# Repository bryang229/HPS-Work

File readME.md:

# About

This is a Clock PCB designed using KiCAD!

The code working with the clock is also included written in the arduino editor!

All parts in the clock are from [this library](https://github.com/hps-matthew/hps-kicad-library) (very useful !).

This is a project under the Hardware Product Spring program ! (Hence HPS) 

More documentation about the code is to come.

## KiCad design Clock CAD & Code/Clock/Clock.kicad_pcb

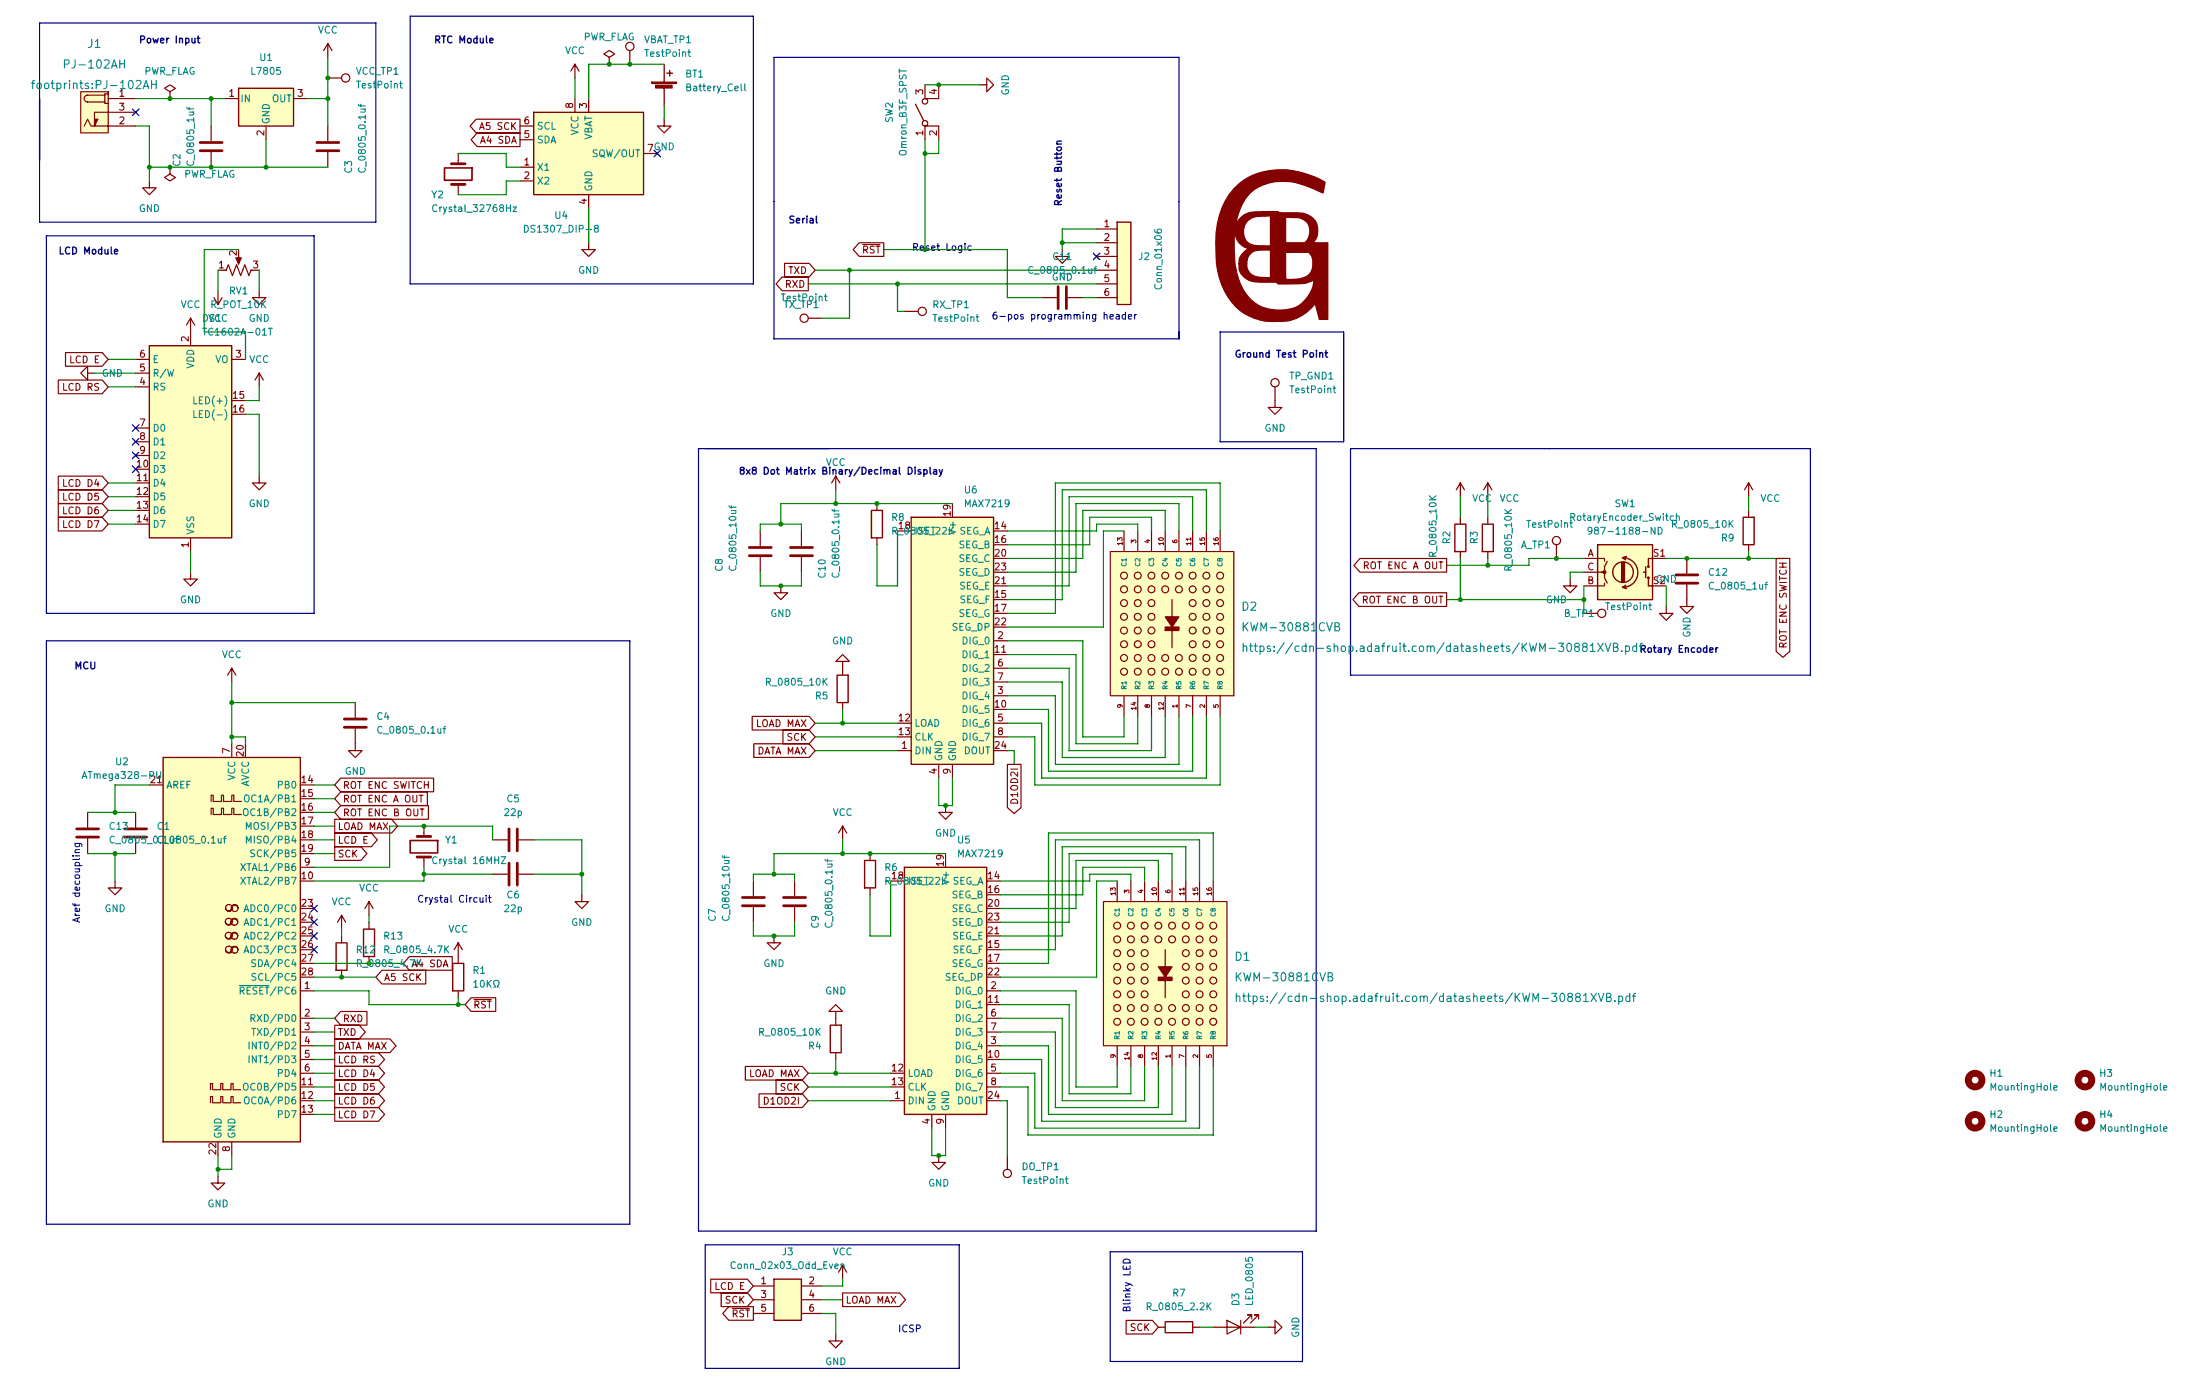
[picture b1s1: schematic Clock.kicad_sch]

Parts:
A_TP1: TestPoint; TestPoint_THTPad_D2.0mm_Drill1.0mm
BT1: Battery_Cell; BatteryHolder_Keystone_106_1x20mm; MPN BS-7; Digikey PN BS-7-ND
B_TP1: TestPoint; TestPoint_THTPad_D2.0mm_Drill1.0mm
C1, C3, C4, C9, C10, C11, C13: C_0805_0.1uf; C_0805_2012Metric; Voltage N/A; Tolerance N/A; MPN 08055C104KAT2A; Digikey PN 478-1395-1-ND
C2, C12: C_0805_1uf; C_0805_2012Metric; Voltage N/A; Tolerance N/A; MPN CC0805KKX7R8BB105; Digikey PN 311-1456-1-ND
C5, C6: 22p; C_0805_2012Metric; Voltage N/A; Tolerance N/A; MPN CC0805JRNPO9BN220; Digikey PN 311-1103-1-ND
C7, C8: C_0805_10uf; C_0805_2012Metric; Voltage N/A; Tolerance N/A; MPN GRM21BR61E106KA73L; Digikey PN 490-5523-1-ND
D1, D2: KWM-30881CVB; MPN KWM-30881CVB; Digikey PN N/A
D3: LED_0805; LED_0805_2012Metric; MPN 150080RS75000; Digikey PN 732-4984-1-ND
DO_TP1: TestPoint; TestPoint_THTPad_D2.0mm_Drill1.0mm
DS1: TC1602A-01T; MPN 1447; Digikey PN 1528-2212-ND
H1, H2, H3, H4: MountingHole; MountingHole_3.2mm_M3
J1: PJ-102AH; MPN PJ-102AH; Digikey PN CP-102AH-ND
J2: Conn_01x06; PinHeader_1x06_P2.54mm_Vertical; MPN 61300611121; Digikey PN 732-5319-ND
J3: Conn_02x03_Odd_Even; PinHeader_2x03_P2.54mm_Vertical; MPN PRPC003DAAN-RC; Digikey PN S2011EC-03-ND
R1: 10KΩ; R_0805_2012Metric; Tolerance N/A; MPN RC0805FR-0710KL; Digikey PN 311-10.0KCRCT-ND
R2, R3, R4, R5, R9: R_0805_10K; R_0805_2012Metric; Tolerance N/A; MPN RC0805FR-0710KL; Digikey PN 311-10.0KCRCT-ND
R6, R8: R_0805_22K; R_0805_2012Metric; Tolerance N/A; MPN RC0805FR-0722KL; Digikey PN 311-22.0KCRCT-ND
R7: R_0805_2.2K; R_0805_2012Metric; Tolerance N/A; MPN N/A; Digikey PN 311-2.20KCRCT-ND
R12, R13: R_0805_4.7K; R_0805_2012Metric; Tolerance N/A; MPN RC0805FR-074K7L; Digikey PN 311-4.70KCRCT-ND
RV1: R_POT_10K; Potentiometer_Bourns_3386P_Vertical; MPN 3386P-1-103TLF; Digikey PN 3386P-103TLF-ND
RX_TP1: TestPoint; TestPoint_THTPad_D2.0mm_Drill1.0mm
SW1: RotaryEncoder_Switch; RotaryEncoder_TT_EN11-Switch_Vertical_H20mm_CircularMountin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; Digikey PN 987-1188-ND
SW2: Omron_B3F_SPST; SW_SPST_Omron_B3FS-100xP; MPN B3FS-1000P; Digikey PN SW423CT-ND
TP_GND1: TestPoint; TestPoint_THTPad_D2.0mm_Drill1.0mm
TX_TP1: TestPoint; TestPoint_THTPad_D2.0mm_Drill1.0mm
U1: L7805; TO-252-2; MPN L7805CDT-TR; Digikey PN 497-7255-1-ND
U2: ATmega328-PU; DIP-28_W7.62mm; MPN ED281DT; Digikey PN ED3050-5-ND
U4: DS1307_DIP-8; DIP-8_W7.62mm; MPN A 08-LC-TT; Digikey PN AE9986-ND
U5, U6: MAX7219; DIP-24_W7.62mm; MPN ED241DT; Digikey PN ED3049-5-ND
VBAT_TP1: TestPoint; TestPoint_THTPad_D2.0mm_Drill1.0mm
VCC_TP1: TestPoint; TestPoint_THTPad_D2.0mm_Drill1.0mm
Y1: Crystal 16MHZ; Crystal_SMD_HC49-SD; MPN ECS-160-20-5PXDN-TR; Digikey PN XC1299CT-ND
Y2: Crystal_32768Hz; Crystal_SMD_2Pin_3.2x1.5mm; MPN Q 0,032768-JTX310-12,5-20-T1-HMR-50K-LF; Digikey PN 1908-1314-1-ND

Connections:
A4 SDA: R13.2, U2.27 (SDA/PC4), U4.5 (SDA)
A5 SCK: R12.2, U2.28 (SCL/PC5), U4.6 (SCL)
D1OD2I: U5.1 (DIN), U6.24 (DOUT)
DATA MAX: U2.4 (INT0/PD2), U6.1 (DIN)
GND: BT1.2 (-), C1.2, C2.2, C3.2, C4.2, C5.2, C6.2, C7.2, C8.2, C9.2, C10.2, C12.1, C13.2, D3.1 (K), DS1.1 (VSS), DS1.5 (R/W), DS1.16 (LED(-)), J1.2 (OUT), J2.1, J2.2, J3.6, R4.2, R5.2, RV1.3, SW1.C, SW1.S2, SW2.3 (B), SW2.4 (B), TP_GND1.1, U1.2 (GND), U2.8 (GND), U2.22 (GND), U4.4 (GND), U5.4 (GND), U5.9 (GND), U6.4 (GND), U6.9 (GND)
LCD D4: DS1.11 (D4), U2.6 (PD4)
LCD D5: DS1.12 (D5), U2.11 (OC0B/PD5)
LCD D6: DS1.13 (D6), U2.12 (OC0A/PD6)
LCD D7: DS1.14 (D7), U2.13 (PD7)
LCD E: DS1.6 (E), J3.1, U2.18 (MISO/PB4)
LCD RS: DS1.4 (RS), U2.5 (INT1/PD3)
LOAD MAX: J3.4, R4.1, R5.1, U2.17 (MOSI/PB3), U5.12 (LOAD), U6.12 (LOAD)
unnamed: BT1.1 (+), U4.3 (VBAT), VBAT_TP1.1
unnamed: C1.1, C13.1, U2.21 (AREF)
unnamed: C2.1, J1.1 (POLE), U1.1 (IN)
unnamed: C5.1, U2.9 (XTAL1/PB6), Y1.1
unnamed: C6.1, U2.10 (XTAL2/PB7), Y1.2
unnamed: C11.2, J2.6
unnamed: D1.1 (R5), U5.3 (DIG_4)
unnamed: D1.2 (R7), U5.5 (DIG_6)
unnamed: D1.3 (C2), U5.14 (SEG_A)
unnamed: D1.4 (C3), U5.16 (SEG_B)
unnamed: D1.5 (R8), U5.8 (DIG_7)
unnamed: D1.6 (C5), U5.23 (SEG_D)
unnamed: D1.7 (R6), U5.10 (DIG_5)
unnamed: D1.8 (R3), U5.6 (DIG_2)
unnamed: D1.9 (R1), U5.2 (DIG_0)
unnamed: D1.10 (C4), U5.20 (SEG_C)
unnamed: D1.11 (C6), U5.21 (SEG_E)
unnamed: D1.12 (R4), U5.7 (DIG_3)
unnamed: D1.13 (C1), U5.22 (SEG_DP)
unnamed: D1.14 (R2), U5.11 (DIG_1)
unnamed: D1.15 (C7), U5.15 (SEG_F)
unnamed: D1.16 (C8), U5.17 (SEG_G)
unnamed: D2.1 (R5), U6.3 (DIG_4)
unnamed: D2.2 (R7), U6.5 (DIG_6)
unnamed: D2.3 (C2), U6.14 (SEG_A)
unnamed: D2.4 (C3), U6.16 (SEG_B)
unnamed: D2.5 (R8), U6.8 (DIG_7)
unnamed: D2.6 (C5), U6.23 (SEG_D)
unnamed: D2.7 (R6), U6.10 (DIG_5)
unnamed: D2.8 (R3), U6.6 (DIG_2)
unnamed: D2.9 (R1), U6.2 (DIG_0)
unnamed: D2.10 (C4), U6.20 (SEG_C)
unnamed: D2.11 (C6), U6.21 (SEG_E)
unnamed: D2.12 (R4), U6.7 (DIG_3)
unnamed: D2.13 (C1), U6.22 (SEG_DP)
unnamed: D2.14 (R2), U6.11 (DIG_1)
unnamed: D2.15 (C7), U6.15 (SEG_F)
unnamed: D2.16 (C8), U6.17 (SEG_G)
unnamed: D3.2 (A), R7.2
unnamed: DO_TP1.1, U5.24 (DOUT)
unnamed: DS1.3 (VO), RV1.2
unnamed: R6.2, U5.18 (ISET)
unnamed: R8.2, U6.18 (ISET)
unnamed: U4.1 (X1), Y2.1
unnamed: U4.2 (X2), Y2.2
ROT ENC A OUT: A_TP1.1, R3.2, SW1.A, U2.15 (OC1A/PB1)
ROT ENC B OUT: B_TP1.1, R2.2, SW1.B, U2.16 (OC1B/PB2)
ROT ENC SWITCH: C12.2, R9.1, SW1.S1, U2.14 (PB0)
RXD: J2.5, RX_TP1.1, U2.2 (RXD/PD0)
SCK: J3.3, R7.1, U2.19 (SCK/PB5), U5.13 (CLK), U6.13 (CLK)
TXD: J2.4, TX_TP1.1, U2.3 (TXD/PD1)
VCC: C3.1, C4.1, C7.1, C8.1, C9.1, C10.1, DS1.2 (VDD), DS1.15 (LED(+)), J3.2, R1.1, R2.1, R3.1, R6.1, R8.1, R9.2, R12.1, R13.1, RV1.1, U1.3 (OUT), U2.7 (VCC), U2.20 (AVCC), U4.8 (VCC), U5.19 (V+), U6.19 (V+), VCC_TP1.1
~RST: C11.1, J3.5, R1.2, SW2.1 (A), SW2.2 (A), U2.1 (~RESET/PC6)

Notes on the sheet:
Ground Test Point
8x8 Dot Matrix Binary/Decimal Display
Power Input
Reset Button
Serial
Blinky LED
ICSP
RTC Module
Rotary Encoder
Aref decoupling
6-pos programming header
Crystal Circuit
LCD Module
MCU
Reset Logic

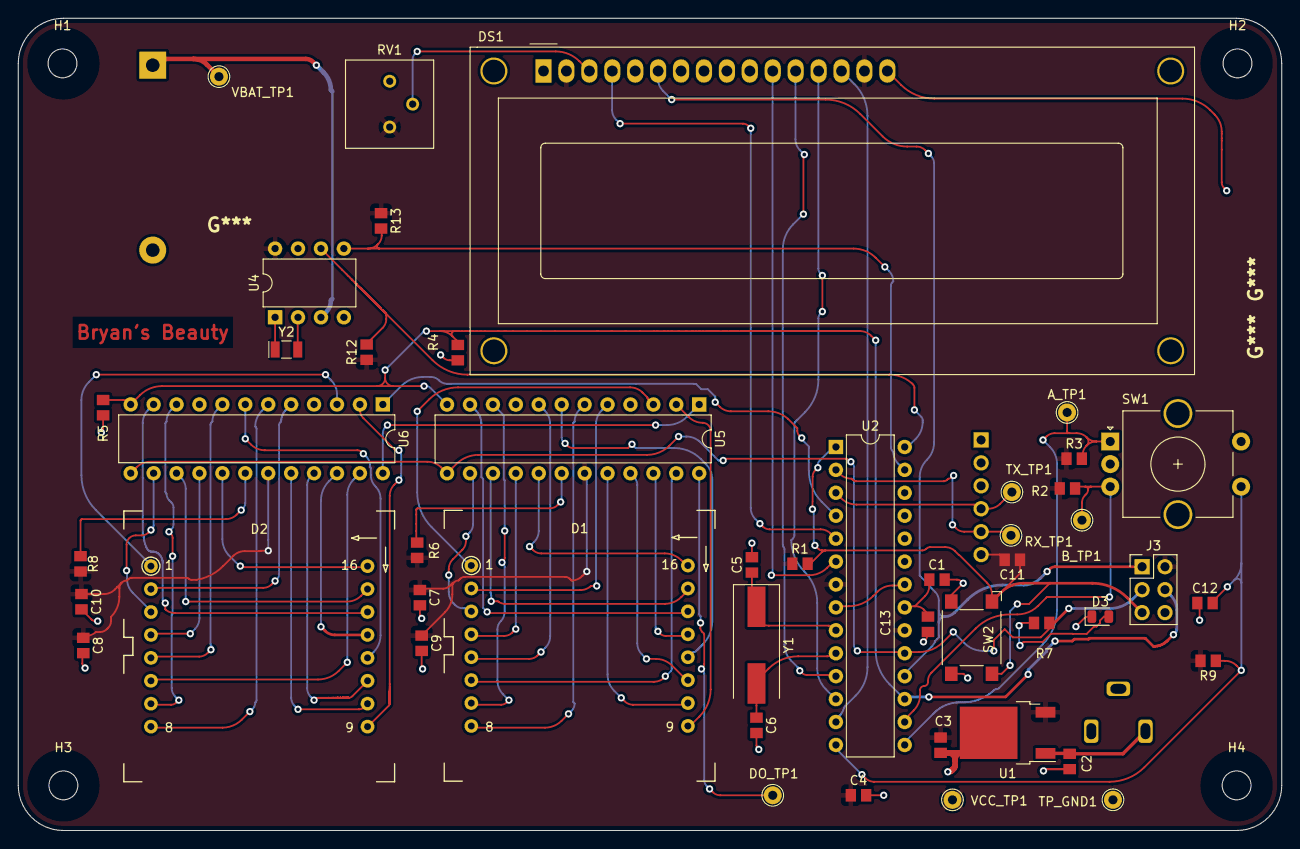
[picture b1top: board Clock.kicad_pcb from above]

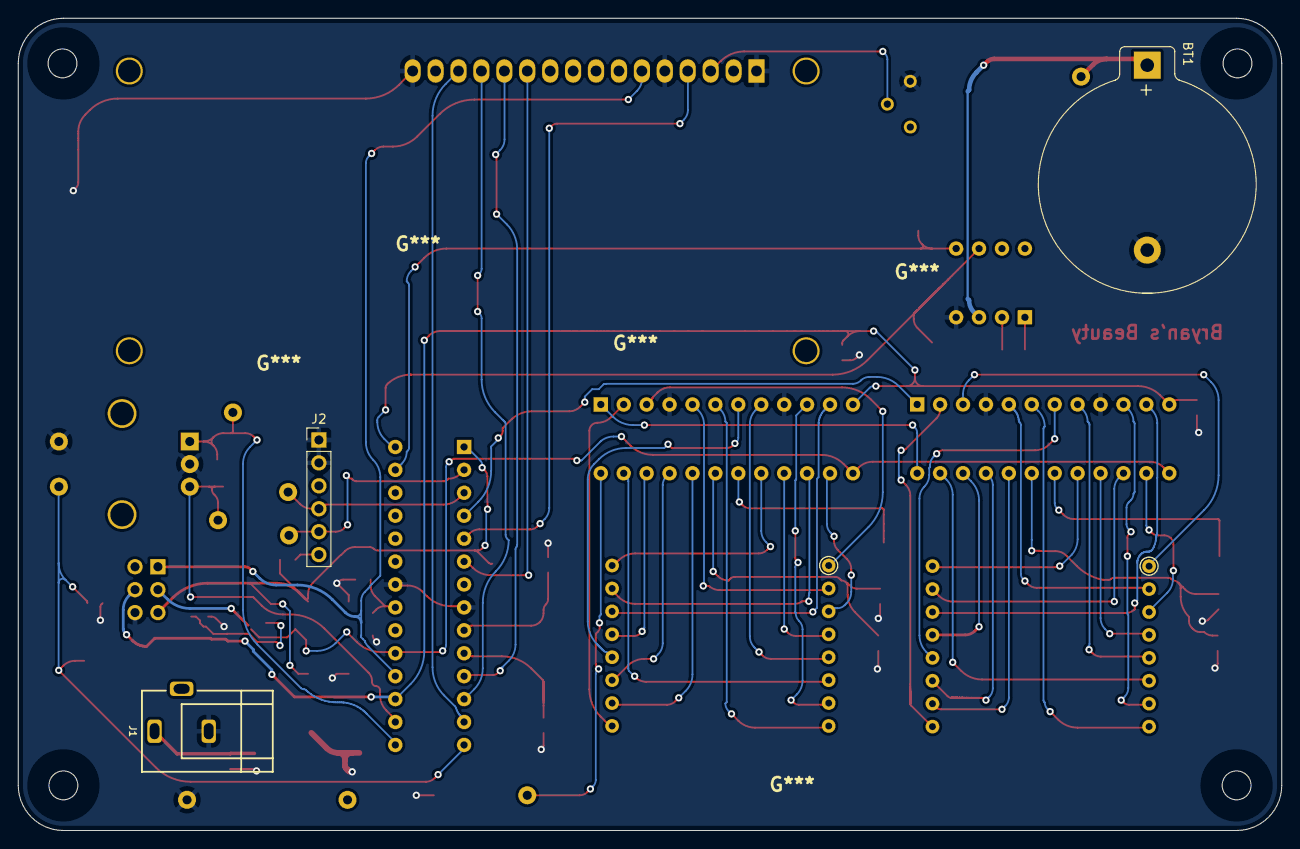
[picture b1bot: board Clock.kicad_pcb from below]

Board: 2 copper layers, 140.0 x 90.0 mm, 54 parts (3 on the bottom side), 65 nets.

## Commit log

2022-06-12 Uploaded Week1
    - Blinking LED code
    - Blinking LED Schema
2022-06-12 Fixed Serial.begin placement
2022-06-21 Week 2 work
    (I forgot to push this earlier oops)
2022-06-27 HMI Design added to KiCAD
    I need the Rotary Encoder for my schema
2022-07-02 Posted Week 4 and Possibly updated week3
2022-07-07 Updated Schema & PCB
    PCB was completely redone with only two DRC warnings which pertain to the Power In but nothing big, Changed to smaller LCD (Thankfully more space)
2022-07-07 Fixed major DRC issues
    Only DRC issues now are due to my logo :(
2022-07-08 Fixed ALL DRC Warnings
    Mark the works of this Github Commit, this clock PCB will be amazing (Added proper logo to PCB and Schema)
2022-07-08 Added Fetus Arduino Code
    Baby Clock Code has been added
2022-07-08 Added MD explaining major errors in code
2022-07-08 Fixed Issue
2022-07-08 Fixed Clock code and added copperto logo
2022-07-12 Week 6 Update* (Arduino Code)
    Added additional Display modes now including Decimal and Binary mode found at https://bryang229.github.io/8x8Demo/ :) now we have 3 different ways to read time !
2022-07-17 Added Rounded Tracing (Passing all DRC)
    It's so perty (pretty :))
2022-07-17 Rot Encoder Update
2022-07-19 Uploading some week 7 work
    DFM Passed with no show stoppers :). I will be pushing a week 7 folder soon with all the good stuff
2022-07-20 Week 7 Update !
    It's great :smile:
2022-07-20 STEP Push
    STEP appears
2022-07-20 Pushed Arduino Code
    Added the code :)
2022-07-20 Fixed PCB & Gerber
    No more backsided SMT
2022-07-20 Fixed weeks
    Week 7 will now hold all future updates to the PCB ! (Including future weeks)
2022-07-20 Applied 12/12 rules
    Fix gerbers as well !
2022-07-21 Rounded Traces Gerber update
2022-07-21 Uploaded Student Designs :)
2022-07-21 Fixed week 7
    Accidentally worked in week 6 again but week 7 is the current folder again
2022-07-22 Late Student Design push
2022-07-22 Image update
2022-07-22 Gave up on weeks
2022-07-22 Fixed DRC and ERC
2022-07-22 Fixed DRC and ERC issues
    Also added 12/12 rules
2022-07-22 Fixed some more issues
2022-07-22 Gerber gerber
2022-07-23 Just a little intro md
2022-07-23 Reuploading Clock Code !
2022-07-24 Fixed Binary conversion in code
    Float conversion to int causes an issue so you need to add one when the float > 3.0
2022-07-24 Fixed small syntax issue
2022-08-14 Renamed README
2022-08-20 Updated code
2022-08-20 Added Test Files
2022-08-20 Added rot lib
